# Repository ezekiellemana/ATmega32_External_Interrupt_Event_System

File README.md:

# ATmega32 External Interrupt Event Counter System

## CT 321 PBL 07 - External Interrupt-Based Emergency Stop and Event Counter System

This repository contains the completed ATmega32 external interrupt emergency stop and event counter system. The project demonstrates event-driven embedded-system control using INT0, INT1, and INT2. The design was verified using SimulIDE, KiCad, MPLAB for VS Code / AVR-GCC compatible firmware, Gerber export, and a recorded demonstration video.

---

## Final Submission Status

| Requirement | Evidence / Location | Status |
| --- | --- | --- |
| System block diagram | `documentation/block_diagram.png` | Complete |
| ATmega32 pin mapping table | `documentation/pin_mapping_table.md` | Complete |
| Firmware flowchart | `documentation/flowchart.png` | Complete |
| KiCad schematic | `kicad/schematic/kicad_schematic.png`, `.pdf`, and `kicad/ATmega32_External_Interrupt_Event_System.kicad_sch` | Complete |
| KiCad PCB layout | `kicad/pcb/kicad_pcb.png` and `kicad/ATmega32_External_Interrupt_Event_System.kicad_pcb` | Complete |
| KiCad PCB 3D view | `kicad/pcb/kicad_pcb_3D.png`, `kicad/pcb/kicad_pcb_3D_2.png` | Complete |
| DRC result | `kicad/pcb/drc_zero_errors.png` | Complete - 0 violations / 0 unconnected items |
| Gerber and drill files | `kicad/gerber/` | Complete |
| Firmware source code | `firmware/src/main.c` | Complete |
| Compiled HEX file | `firmware/hex/emergency_event_counter.hex` | Complete |
| SimulIDE circuit | `simulide/circuit/emergency_event_counter.sim1` | Complete |
| SimulIDE screenshots | `simulide/screenshots/` | Complete - 7 tests captured |
| Test results table | `documentation/test_results.md` | Complete |
| Final report DOCX | `documentation/final_report/CT_321_PBL_07_Group07_Final_Report.docx` | Complete |
| Final report PDF | `documentation/final_report/CT_321_PBL_07_Group07_Final_Report.pdf` | Complete |
| PowerPoint presentation | `documentation/CT_321_PBL_07_Group07_Presentation.pptx` | Complete |
| Demonstration video | `media/demo_video.mp4` | Complete |

---

## Circuit and PCB Images

### Schematic

### PCB Layout (2D)

### PCB 3D View

---

## System Behaviour

| Action | Expected Result |
| --- | --- |
| System powered ON | Green LED ON, red LED OFF, buzzer OFF, serial count = 0 |
| Event pulse on INT1 | Event count increases only in normal mode |
| Emergency stop on INT0 | Red LED and buzzer ON, green LED OFF, counting stops |
| Event during emergency | Count does not increase |
| Recovery on INT2 during emergency | System returns to normal mode and keeps the current count |
| Recovery/reset on INT2 during normal mode | Event count resets to zero |

---

## Important Simulation Settings

```text
MCU: ATmega32 / ATmega32A
Clock: 8 MHz
HEX file: firmware/hex/emergency_event_counter.hex
UART: 9600 baud, 8 data bits, 1 stop bit
Inputs: active LOW buttons with pull-ups
RESET: held HIGH during normal running
```

---

## Folder Structure

```text
ATmega32_External_Interrupt_Event_System/
|-- README.md
|-- firmware/
|   |-- src/main.c
|   |-- include/
|   `-- hex/emergency_event_counter.hex
|-- kicad/
|   |-- ATmega32_External_Interrupt_Event_System.kicad_pro
|   |-- ATmega32_External_Interrupt_Event_System.kicad_sch
|   |-- ATmega32_External_Interrupt_Event_System.kicad_pcb
|   |-- schematic/
|   |-- pcb/
|   `-- gerber/
|-- simulide/
|   |-- circuit/emergency_event_counter.sim1
|   `-- screenshots/
|-- documentation/
|   |-- CT_321_PBL_07_Group07_Presentation.pptx
|   |-- block_diagram.png
|   |-- flowchart.png
|   |-- interrupt_configuration.md
|   |-- pin_mapping_table.md
|   |-- test_results.md
|   `-- final_report/
|       |-- CT_321_PBL_07_Group07_Final_Report.docx
|       `-- CT_321_PBL_07_Group07_Final_Report.pdf
`-- media/
    |-- demo_video.mp4
    `-- demonstration_video_link.txt
```

---

## Demonstration Summary

The final simulation and video demonstrate normal startup, single event counting, multiple event counting, emergency stop, lockout of event counting during emergency mode, recovery back to normal mode, and reset of the count in normal mode.

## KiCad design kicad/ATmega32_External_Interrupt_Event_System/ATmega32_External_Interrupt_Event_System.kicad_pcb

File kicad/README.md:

# KiCad Schematic, PCB Layout, and Gerber Files

## Status

The KiCad part of this project is complete.

```text
ERC: Passed with zero errors
DRC: Passed with zero violations and zero unconnected items
Gerber files: Exported
Drill files: Exported
```

---

## KiCad Source Files

Open this project in KiCad:

```text
kicad/ATmega32_External_Interrupt_Event_System/ATmega32_External_Interrupt_Event_System.kicad_pro
```

Main design files:

```text
kicad/ATmega32_External_Interrupt_Event_System/ATmega32_External_Interrupt_Event_System.kicad_sch
kicad/ATmega32_External_Interrupt_Event_System/ATmega32_External_Interrupt_Event_System.kicad_pcb
```

---

## Schematic Evidence

The schematic export is saved here:

```text
kicad/schematic/kicad_schematic.png
kicad/schematic/kicad_schematic.pdf
```

The schematic includes:

- ATmega32A-P microcontroller
- INT0 emergency stop button
- INT1 event pulse button
- INT2 recovery/reset button
- MCU reset button
- Green and red LEDs
- Buzzer driver using NPN transistor
- 8 MHz crystal with two 22 pF capacitors
- VCC, AVCC, GND, reset circuit, and decoupling capacitors
- External 10 kΩ pull-up resistors for the three interrupt inputs
- Serial header for UART TX

---

## PCB Evidence

The PCB screenshot and DRC evidence are saved here:

```text
kicad/pcb/kicad_pcb.png
kicad/pcb/drc_zero_errors.png
```

The PCB uses:

- F.Cu copper zone for +5V
- B.Cu copper zone for GND
- Through-hole components
- Clear silkscreen labels for buttons, LEDs, buzzer, and header
- Fully routed nets with no unconnected items

---

## Gerber Files

Gerber and drill files are saved here:

```text
kicad/gerber/
```

Required fabrication outputs included:

```text
ATmega32_External_Interrupt_Event_System-F_Cu.gbr
ATmega32_External_Interrupt_Event_System-B_Cu.gbr
ATmega32_External_Interrupt_Event_System-F_Silkscreen.gbr
ATmega32_External_Interrupt_Event_System-B_Silkscreen.gbr
ATmega32_External_Interrupt_Event_System-F_Mask.gbr
ATmega32_External_Interrupt_Event_System-B_Mask.gbr
ATmega32_External_Interrupt_Event_System-Edge_Cuts.gbr
ATmega32_External_Interrupt_Event_System-PTH.drl
ATmega32_External_Interrupt_Event_System-NPTH.drl
ATmega32_External_Interrupt_Event_System-job.gbrjob
ATmega32_Gerber_Files.zip
```

---

## Final KiCad Checklist

- [x] ATmega32 schematic created
- [x] External interrupt buttons connected
- [x] Output LEDs and buzzer connected
- [x] Reset, crystal, power, and decoupling included
- [x] Footprints assigned
- [x] PCB routed
- [x] GND and +5V zones added
- [x] DRC passed with zero errors
- [x] Gerber files exported
- [x] Drill files exported

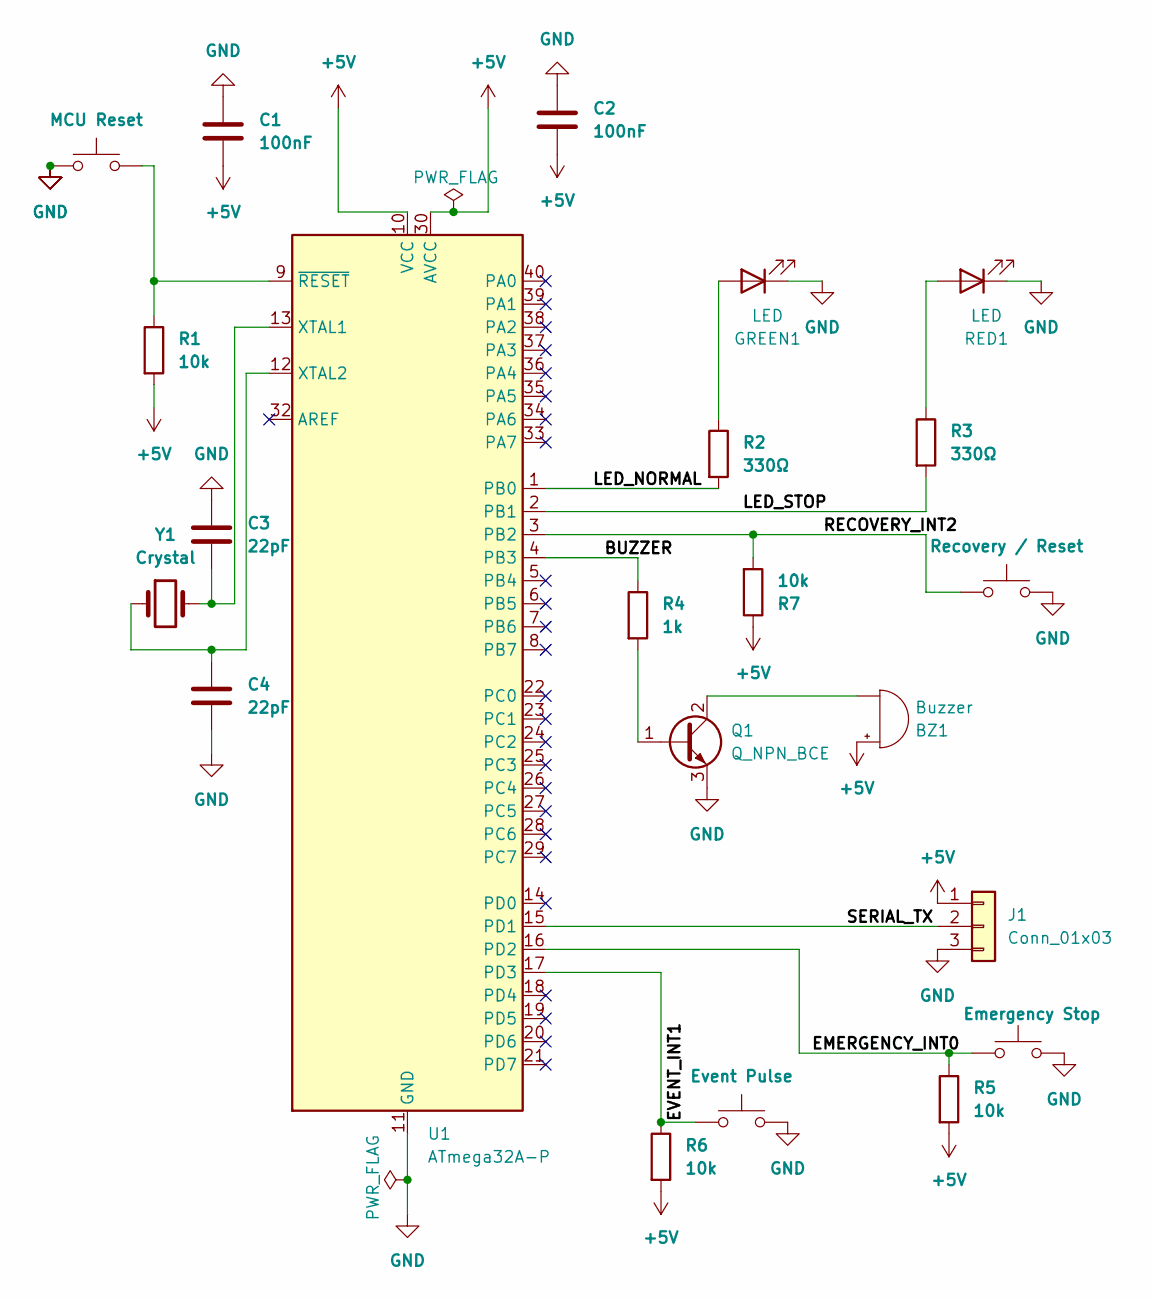
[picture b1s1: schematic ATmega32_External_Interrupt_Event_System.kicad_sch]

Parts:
BZ1: Buzzer; Buzzer_12x9.5RM7.6
C1, C2: 100nF; C_Disc_D5.0mm_W2.5mm_P5.00mm
C3, C4: 22pF; C_Disc_D5.0mm_W2.5mm_P5.00mm
EventPulse1: Event Pulse; SW_PUSH_6mm
GREEN1: LED; LED_D5.0mm
J1: Conn_01x03; PinHeader_1x03_P2.54mm_Vertical
MCU-Reset1: MCU Reset; SW_PUSH_6mm
Q1: Q_NPN_BCE; TO-92_Inline
R1, R5, R6, R7: 10k; R_Axial_DIN0207_L6.3mm_D2.5mm_P7.62mm_Horizontal
R2, R3: 330Ω; R_Axial_DIN0207_L6.3mm_D2.5mm_P7.62mm_Horizontal
R4: 1k; R_Axial_DIN0207_L6.3mm_D2.5mm_P7.62mm_Horizontal
RED1: LED; LED_D5.0mm
SW1: Emergency Stop; SW_PUSH_6mm
SW3: Recovery / Reset; SW_PUSH_6mm
U1: ATmega32A-P; DIP-40_W15.24mm
Y1: Crystal; Crystal_HC49-4H_Vertical

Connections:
+5V: BZ1.1 (+), C1.2, C2.2, J1.1, R1.2, R5.2, R6.2, R7.1, U1.10 (VCC), U1.30 (AVCC)
/ EVENT_INT1: EventPulse1.1, R6.1, U1.17 (PD3)
/BUZZER: R4.1, U1.4 (PB3)
/EMERGENCY_INT0: R5.1, SW1.1, U1.16 (PD2)
/LED_NORMAL: R2.2, U1.1 (PB0)
/LED_STOP: R3.2, U1.2 (PB1)
/RECOVERY_INT2: R7.2, SW3.1, U1.3 (PB2)
/SERIAL_TX: J1.2, U1.15 (PD1)
GND: C1.1, C2.1, C3.1, C4.2, EventPulse1.2, GREEN1.1 (K), J1.3, MCU-Reset1.1, Q1.3 (E), RED1.1 (K), SW1.2, SW3.2, U1.11 (GND), U1.31 (GND); also elsewhere on the board
unnamed: BZ1.2 (-), Q1.2 (C)
unnamed 10: GREEN1.2 (A), R2.1; also elsewhere on the board
unnamed: Q1.1 (B), R4.2
unnamed: R3.1, RED1.2 (A)
unnamed: C3.2, U1.13 (XTAL1), Y1.2
unnamed: C4.1, U1.12 (XTAL2), Y1.1
unnamed: MCU-Reset1.2, R1.1, U1.9 (~RESET)

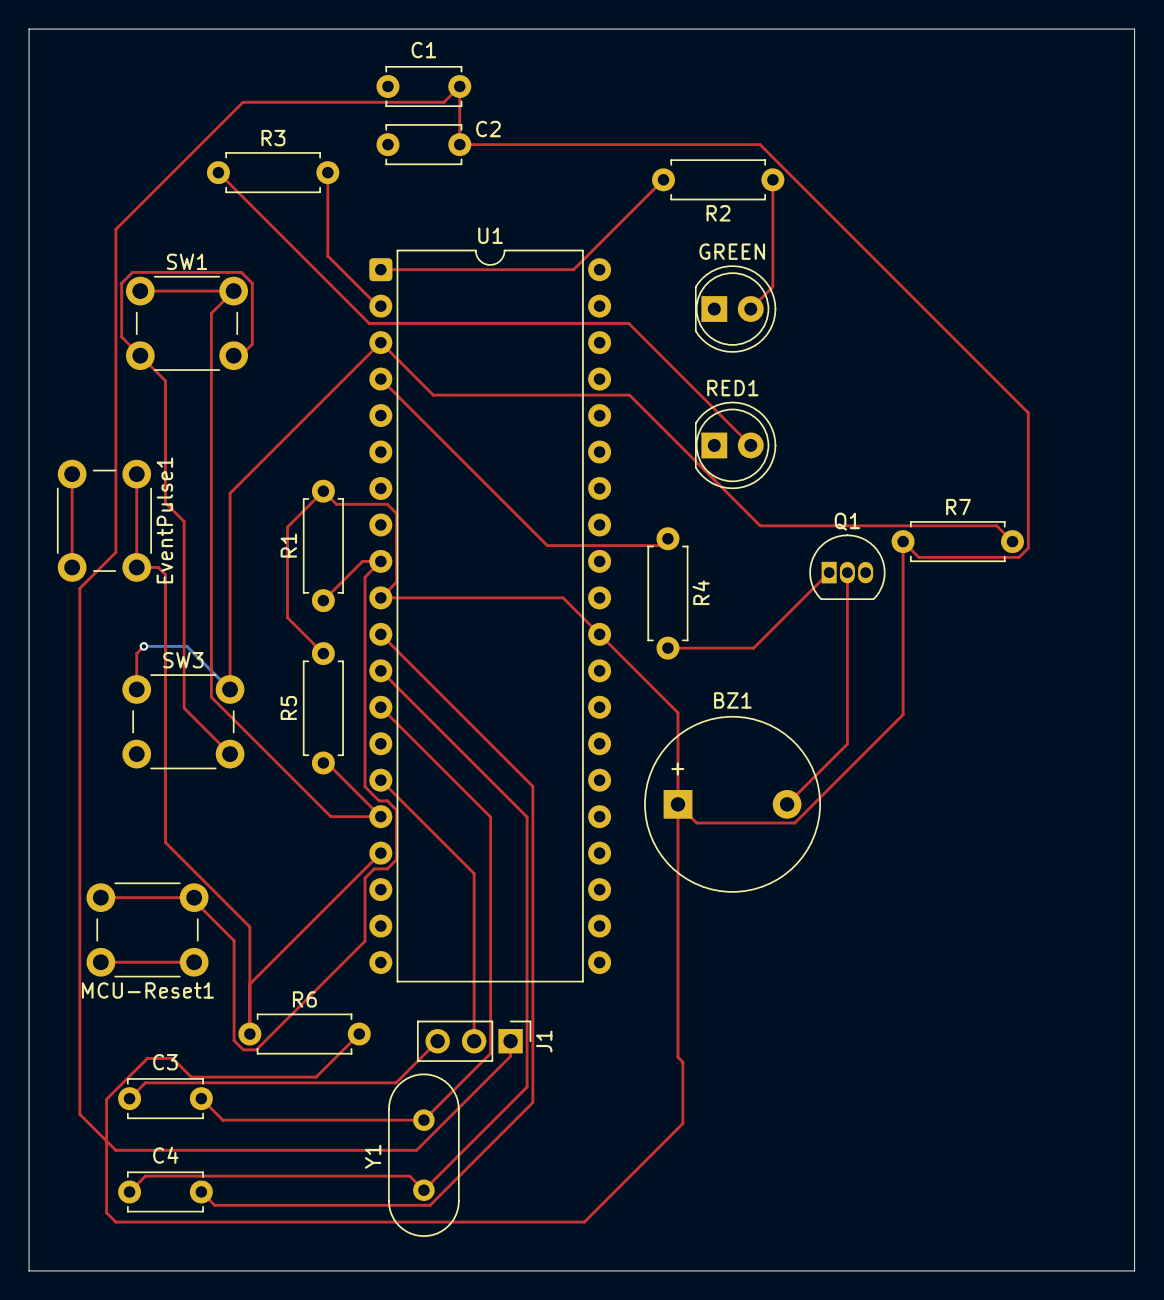
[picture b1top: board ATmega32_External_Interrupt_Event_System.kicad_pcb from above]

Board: 2 copper layers, 77.0 x 86.5 mm, 22 parts (0 on the bottom side), 16 nets.

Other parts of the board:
GREEN: LED; LED_D5.0mm

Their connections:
GND: GREEN.1 (K); also elsewhere on the board
unnamed 10: GREEN.2 (A); also elsewhere on the board

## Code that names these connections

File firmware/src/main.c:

/*
 * CT 321 PBL 07
 * Project: External Interrupt-Based Emergency Stop and Event Counter System
 * Target MCU: ATmega32
 * Clock: 8 MHz
 * IDE: MPLAB for VS Code / AVR-GCC compatible toolchain
 *
 * INT0 (PD2): Emergency stop button, active LOW
 * INT1 (PD3): Event pulse sensor/button, active LOW
 * INT2 (PB2): Recovery/reset button, active LOW
 * PB0: Green LED, PB1: Red LED, PB3: Buzzer
 * PD1/TXD: Serial output for event count
 */

#define F_CPU 8000000UL

#include <avr/io.h>
#include <avr/interrupt.h>
#include <stdint.h>

#define DEBOUNCE_MS 200UL
#define LED_NORMAL  PB0
#define LED_STOP    PB1
#define BUZZER      PB3

volatile uint16_t event_count = 0;
volatile uint8_t emergency_mode = 0;
volatile uint8_t display_update_required = 1;
volatile uint32_t system_ms = 0;
volatile uint32_t last_int0_ms = 0;
volatile uint32_t last_int1_ms = 0;
volatile uint32_t last_int2_ms = 0;

static void uart_send_char(char c)
{
    while (!(UCSRA & (1 << UDRE))) {
        ;
    }
    UDR = c;
}

static void uart_send_text(const char *text)
{
    while (*text) {
        uart_send_char(*text++);
    }
}

static void uart_send_uint16(uint16_t value)
{
    char buffer[6];
    uint8_t index = 0;

    if (value == 0) {
        uart_send_char('0');
        return;
    }

    while (value > 0 && index < sizeof(buffer)) {
        buffer[index++] = (value % 10) + '0';
        value = value / 10;
    }

    while (index > 0) {
        uart_send_char(buffer[--index]);
    }
}

static void uart_init(void)
{
    /* 9600 baud at 8 MHz, normal speed: UBRR = 51 */
    UBRRH = 0;
    UBRRL = 51;
    UCSRB = (1 << TXEN);
    UCSRC = (1 << URSEL) | (1 << UCSZ1) | (1 << UCSZ0);
}

static void timer0_init(void)
{
    /* CTC mode, prescaler 64. 8 MHz / 64 = 125 kHz; OCR0 = 124 gives 1 ms. */
    TCCR0 = (1 << WGM01) | (1 << CS01) | (1 << CS00);
    OCR0 = 124;
    TIMSK |= (1 << OCIE0);
}

static void gpio_init(void)
{
    /* Interrupt inputs with internal pull-up resistors enabled. */
    DDRD &= ~((1 << PD2) | (1 << PD3));
    PORTD |= (1 << PD2) | (1 << PD3);

    DDRB &= ~(1 << PB2);
    PORTB |= (1 << PB2);

    /* Output pins for LEDs and buzzer. */
    DDRB |= (1 << LED_NORMAL) | (1 << LED_STOP) | (1 << BUZZER);
    PORTB &= ~((1 << LED_NORMAL) | (1 << LED_STOP) | (1 << BUZZER));
}

static void external_interrupts_init(void)
{
    /* INT0 falling edge: ISC01 = 1, ISC00 = 0 */
    MCUCR |= (1 << ISC01);
    MCUCR &= ~(1 << ISC00);

    /* INT1 falling edge: ISC11 = 1, ISC10 = 0 */
    MCUCR |= (1 << ISC11);
    MCUCR &= ~(1 << ISC10);

    /* INT2 falling edge: ISC2 = 0 */
    MCUCSR &= ~(1 << ISC2);

    /* Clear any pending interrupt flags before enabling. */
    GIFR |= (1 << INTF0) | (1 << INTF1) | (1 << INTF2);

    /* Enable INT0, INT1 and INT2. */
    GICR |= (1 << INT0) | (1 << INT1) | (1 << INT2);
}

static void update_outputs(uint8_t emergency)
{
    if (emergency) {
        PORTB &= ~(1 << LED_NORMAL);
        PORTB |= (1 << LED_STOP) | (1 << BUZZER);
    } else {
        PORTB |= (1 << LED_NORMAL);
        PORTB &= ~((1 << LED_STOP) | (1 << BUZZER));
    }
}

static void print_status(uint16_t count, uint8_t emergency)
{
    uart_send_text("Mode: ");
    uart_send_text(emergency ? "EMERGENCY STOP" : "NORMAL");
    uart_send_text(" | Count: ");
    uart_send_uint16(count);
    uart_send_text("\r\n");
}

ISR(TIMER0_COMP_vect)
{
    system_ms++;
}

ISR(INT0_vect)
{
    uint32_t now = system_ms;

    if ((now - last_int0_ms) >= DEBOUNCE_MS) {
        emergency_mode = 1;
        display_update_required = 1;
        last_int0_ms = now;
    }
}

ISR(INT1_vect)
{
    uint32_t now = system_ms;

    if ((now - last_int1_ms) >= DEBOUNCE_MS) {
        if (!emergency_mode) {
            event_count++;
            display_update_required = 1;
        }
        last_int1_ms = now;
    }
}

ISR(INT2_vect)
{
    uint32_t now = system_ms;

    if ((now - last_int2_ms) >= DEBOUNCE_MS) {
        if (emergency_mode) {
            emergency_mode = 0;
        } else {
            event_count = 0;
        }
        display_update_required = 1;
        last_int2_ms = now;
    }
}

int main(void)
{
    uint16_t local_count;
    uint8_t local_emergency;

    gpio_init();
    uart_init();
    timer0_init();
    external_interrupts_init();

    sei();

    uart_send_text("ATmega32 External Interrupt Event Counter System\r\n");

    while (1) {
        if (display_update_required) {
            cli();
            local_count = event_count;
            local_emergency = emergency_mode;
            display_update_required = 0;
            sei();

            update_outputs(local_emergency);
            print_status(local_count, local_emergency);
        }
    }

    return 0;
}

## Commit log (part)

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2026-06-14 Created ATmega32 external interrupt event system project
    - Initialised repository structure for CT 321 PBL 07 assignment
    - Added project README with hardware list, pin table, build instructions,
    SimulIDE guide, test procedure, folder map, and submission status
    - Added .gitignore excluding *.elf, *.o, *.d, build/, dist/, .cache/
2026-06-14 Updated README with GitHub repository link
    - Added ezekiellemana/ATmega32_External_Interrupt_Event_System repo URL
    - Fixed bare URLs to markdown link syntax (MD034)
    - Marked GitHub repository as Published in submission status table
2026-06-14 Improved firmware for SimulIDE testing
    - update_outputs() now called every main loop iteration (not only on events)
    so LEDs and buzzer respond immediately when simulation starts
    - Added 1000 ms heartbeat: serial status printed every second even with
    no button activity, confirming the simulation is running
    - Added "System started" startup banner
    - Initial status line printed immediately before entering the main loop
2026-06-14 Restore final assignment firmware
    - main.c confirmed as assignment firmware (heartbeat + interrupt version)
    - emergency_event_counter.hex rebuilt from assignment main.c
    Program: 1403 bytes (4.3%), Data: 80 bytes (3.9%)
    - Added main_assignment_backup.c as a reference copy of assignment firmware
    - Added diagnostic_test.hex (simple blink/UART test used to verify SimulIDE)
2026-06-16 Final CT321 Group 7 submission package
2026-06-17 Remove unnecessary files from final submission
2026-06-17 Add KiCad PCB 3D view images and embed circuit images in README
2026-06-28 Align project structure with assignment spec and remove redundant files
2026-06-28 Add PowerPoint presentation for CT321 Group 7 project
